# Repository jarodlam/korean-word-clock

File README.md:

# Korean word clock
A wall-mounted clock that reads out the current time in Korean.

## Bill of materials
* Raspberry Pi Pico
    * [Core Electronics](https://core-electronics.com.au/raspberry-pi-pico.html)
* Pimoroni RV3028 Breakout
    * [Core Electronics](https://core-electronics.com.au/pimoroni-rv3028-real-time-clock-rtc-breakout.html)
* Adafruit USB-C Breakout
    * [Core Electronics](https://core-electronics.com.au/adafruit-usb-c-breakout-board-downstream-connection.html)
* 1000 uF electrolytic capacitor
    * [Core Electronics](https://core-electronics.com.au/electrolytic-decoupling-capacitors-1000uf-25v.html)
* 1N4733A 5.1 V Zener diode
    * [Core Electronics](https://core-electronics.com.au/zener-diode-5-1v-1w.html)
    * [Jaycar](https://www.jaycar.com.au/5-1v-1n4733-1-watt-zener-diode/p/ZR1403)
* LED 3-pin JST-SM pigtail connectors
    * [Core Electronics](https://core-electronics.com.au/led-strip-pigtail-connector-3-pin.html)
* 12mm momentary push button
    * [Core Electronics](https://core-electronics.com.au/momentary-push-button-switch-12mm-square.html)
    * [Jaycar](https://www.jaycar.com.au/spst-pcb-mount-tactile-switch-round/p/SP0609)

## Translations
Korean | English
------ | -------
한시 | one o'clock
두시 | two o'clock
세시 | three o'clock
네시 | four o'clock
다섯시 | five o'clock
여섯시 | six o'clock
일곱시 | seven o'clock
여덟시 | eight o'clock
아홉시 | nine o'clock
열시 | ten o'clock
열한시 | eleven o'clock
열두시 | twelve o'clock
자정 | midnight
정오 | noon
오분 | five minutes
십분 | ten minutes
이십분 | twenty minutes
삼십분 | thirty minutes
사십분 | forty minutes
오십분 | fifty minutes

## Acknowledgements
* [HangulClock](https://suapapa.github.io/site-hangulclocks/) by Homin Lee
* [Raspberry Pi Pico EAGLE library](https://github.com/Lobo-T/RPI-Pico-Eagle-lib) by Lobo-T
* [pi_pico_neopixel](https://github.com/blaz-r/pi_pico_neopixel) MicroPython library by Blaž Rolih
* [rv3028-python](https://github.com/pimoroni/rv3028-python) MicroPython library by Pimoroni

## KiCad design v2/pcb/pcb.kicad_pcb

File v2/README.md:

# Korean word clock v2
A wall-mounted clock that reads out the current time in Korean.

Change log from v1:
- Uses an ATmega32U4 microcontroller instead of the RP2040. 
- PCB is drawn in KiCad instead of EAGLE.

## Bill of materials
* SparkFun Qwiic Pro Micro
    * [Core Electronics](https://core-electronics.com.au/sparkfun-qwiic-pro-micro-usb-c-atmega32u4.html)
    * [Mouser](https://au.mouser.com/ProductDetail/SparkFun/DEV-15795?qs=vHuUswq2%252BszUNhUhTg0rsg%3D%3D)
* Pimoroni RV3028 Breakout
    * [Core Electronics](https://core-electronics.com.au/pimoroni-rv3028-real-time-clock-rtc-breakout.html)
    * [Mouser](https://au.mouser.com/ProductDetail/Pimoroni/PIM449?qs=GedFDFLaBXE4W0MVwPUjCA%3D%3D)
* LED 3-pin JST-SM pigtail connector
    * [Core Electronics](https://core-electronics.com.au/led-strip-pigtail-connector-3-pin.html)
    * [Mouser](https://au.mouser.com/ProductDetail/Adafruit/1663?qs=GURawfaeGuBbzkAfeSrhnA%3D%3D)
* 12mm momentary push buttons
    * [Core Electronics](https://core-electronics.com.au/momentary-push-button-switch-12mm-square.html)
    * [Mouser](https://au.mouser.com/ProductDetail/SparkFun/COM-09190?qs=WyAARYrbSnYmfgv9mXV0oQ%3D%3D)
    * [Jaycar](https://www.jaycar.com.au/spst-pcb-mount-tactile-switch-round/p/SP0609)
* 4.7k resistors 1.6x3.6 mm
    * [Mouser](https://au.mouser.com/ProductDetail/YAGEO/MFR25SFTF52-4K7?qs=sGAEpiMZZMtlubZbdhIBIGLlr6zM66%2Fae5%252BGZlJpQLw%3D)

## Software

Requirements:

- [PlatformIO](https://platformio.org/)

Usage (run from `src/` directory with `platformio.ini`:

```sh
# Build
$ pio run

# Upload
$ pio run -t upload

# Generate clangd compile_commands.json for LSP
$ pio run -t compiledb -e sparkfun_promicro16

# Clean build files
$ pio run -t clean

# Run local tests
$ pio test -e native

# View serial monitor
$ pio device monitor
```

## Translations
Korean | English
------ | -------
한시 | one o'clock
두시 | two o'clock
세시 | three o'clock
네시 | four o'clock
다섯시 | five o'clock
여섯시 | six o'clock
일곱시 | seven o'clock
여덟시 | eight o'clock
아홉시 | nine o'clock
열시 | ten o'clock
열한시 | eleven o'clock
열두시 | twelve o'clock
자정 | midnight
정오 | noon
오분 | five minutes
십분 | ten minutes
이십분 | twenty minutes
삼십분 | thirty minutes
사십분 | forty minutes
오십분 | fifty minutes

## Acknowledgements and references
* [HangulClock](https://suapapa.github.io/site-hangulclocks/) by Homin Lee
* [Adafruit NeoPixel library](https://github.com/adafruit/Adafruit_NeoPixel)
* [SparkFun KiCad Libraries](https://github.com/sparkfun/SparkFun-KiCad-Libraries)

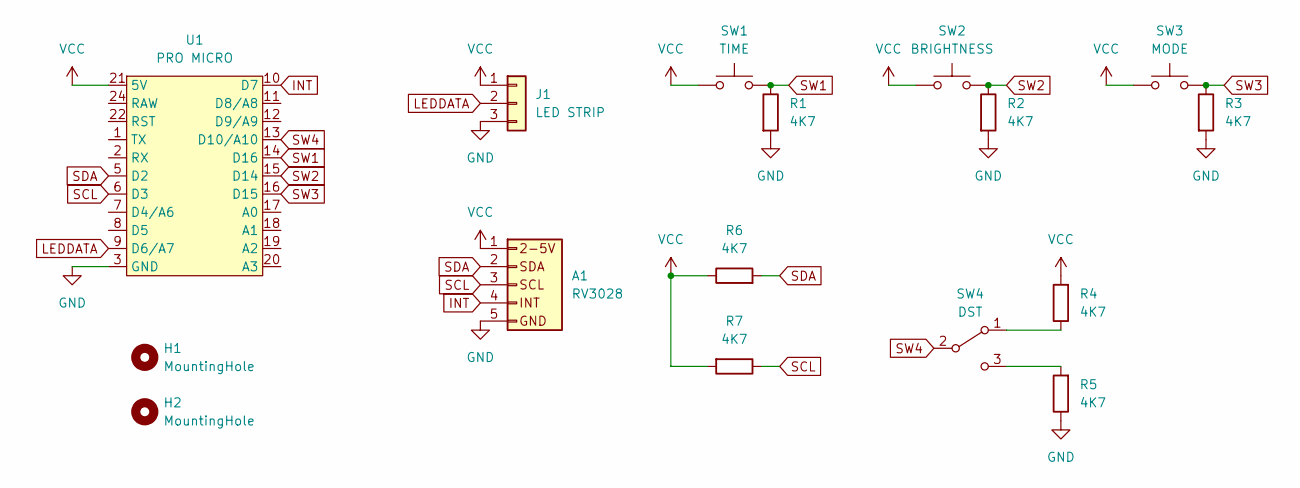
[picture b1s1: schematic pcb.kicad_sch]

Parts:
A1: RV3028; Pimoroni_RV3028_Breakout
H1, H2: MountingHole; MountingHole_3.2mm_M3_Pad
J1: LED STRIP; SolderWire-0.75sqmm_1x03_P4.8mm_D1.25mm_OD2.3mm
R1, R2, R3, R4, R5, R6, R7: 4K7; R_Axial_DIN0204_L3.6mm_D1.6mm_P5.08mm_Horizontal
SW1: TIME; Push_PTH_12x12mm; Mfg Part# EG4904TR-ND
SW2: BRIGHTNESS; Push_PTH_12x12mm; Mfg Part# EG4904TR-ND
SW3: MODE; Push_PTH_12x12mm; Mfg Part# EG4904TR-ND
SW4: DST; Slide_SPDT_PTH_11.6x4.0mm
U1: PRO MICRO; ProMicroC

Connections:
GND: A1.5, J1.3, R1.2, R2.2, R3.2, R5.1, U1.3 (GND), U1.4 (GND), U1.23 (GND)
INT: A1.4, U1.10 (D7)
LEDDATA: J1.2, U1.9 (D6/A7)
unnamed: R4.1, SW4.1 (A)
unnamed: R5.2, SW4.3 (C)
SCL: A1.3, R7.1, U1.6 (D3)
SDA: A1.2, R6.2, U1.5 (D2)
SW1: R1.1, SW1.2, U1.14 (D16)
SW2: R2.1, SW2.2, U1.15 (D14)
SW3: R3.1, SW3.2, U1.16 (D15)
SW4: SW4.2 (B), U1.13 (D10/A10)
VCC: A1.1, J1.1, R4.2, R6.1, R7.2, SW1.1, SW2.1, SW3.1, U1.21 (5V)

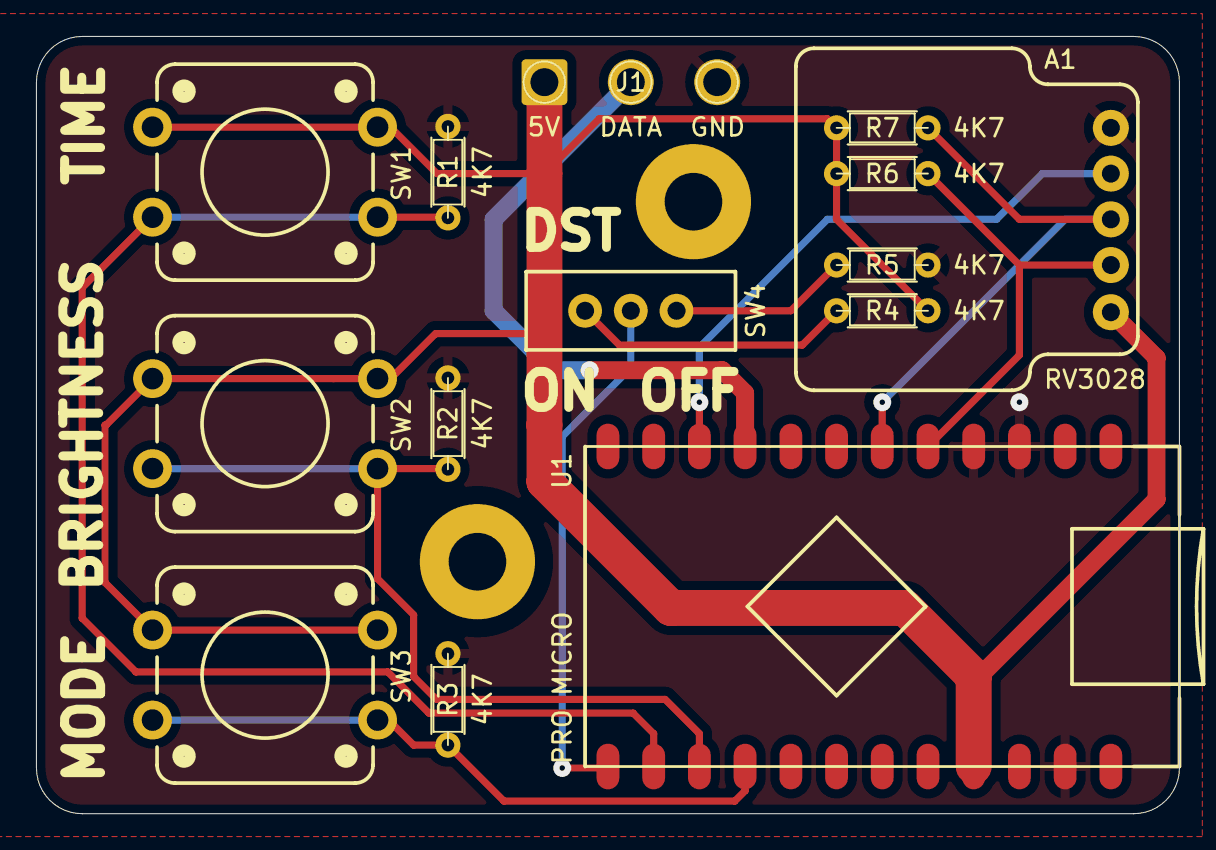
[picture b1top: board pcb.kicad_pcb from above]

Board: 2 copper layers, 63.5 x 43.2 mm, 16 parts (0 on the bottom side), 12 nets.

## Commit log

2022-06-14 [CAD] CAD work in progress
2022-06-14 [CAD] Layer 2 and 3
2022-06-14 [CAD] Most layers done
2022-07-05 [PCB] Initial commit for PCB
2022-08-25 [CAD] Finish 3D design
2022-08-27 [DOC] Updated BOM
2022-08-29 [PCB] Finished design subject to testing
2022-08-29 [DOC] Translations and updated BOM
2022-08-30 [PCB] Sent off for manufacturing
2022-08-30 [CAD] Cutout size for PCB
2022-08-30 [SRC] Start on code
2022-08-30 [DOC] More translations
2022-09-14 [CAD] Mostly final design, need to fix front grid spacing
2022-09-14 [LASER] Start work on laser layout
2022-09-14 [CAD] Fix grid spacing
2022-09-14 [LASER] Final layout
2022-09-24 [SRC] RV2038 interface class
2022-09-24 [SRC] ClockFace class and effects
2022-09-25 [SRC] Button hook up and fast-forwarding
2022-09-25 [SRC] Move ButtonInput to a separate file
2022-09-25 [SRC] Scheduling system
2022-09-25 [SRC] Birthday effect and better rainbow effect
2022-09-30 [SRC] Set time script
2022-09-30 [SRC] Save settings to RTC EEPROM and more effects
2022-10-04 [SRC] Switch daylight savings on/off using switch
2023-06-25 [DOC] Change title
2024-11-22 [CHORE] Add v2
2024-11-22 [PCB] Start v2 PCB
2024-11-22 [DOC] Add additional BOM
2024-11-27 [PCB] New PCB mostly complete
2024-11-29 [DOC] Correct resistor
2024-11-29 [PCB] Final design and gerber
2025-01-11 [SRC] Button implementation
2025-01-12 [SRC] Port RV3028 library
2025-01-12 [SRC] RTC fully working
2025-03-29 [SRC] LED matrix code
2025-09-28 [SRC] Use PlatformIO
2025-09-28 [SRC] Run clang-format
2025-10-01 [SRC] Add Nix
2025-10-04 wip 2
2025-10-04 wip 3
2025-10-04 wip 4 (working)
2025-10-05 uploading!
2025-10-05 it works
2025-10-05 [SRC] KoreanClockFace implementation, refactor, tests
    wip 2
    wip 3
    wip 4 (working)
    uploading!
    it works
2025-10-05 [CHORE] Add Nix
2025-10-26 [SRC] clang-format
2025-10-27 [SRC] buttons wip
2025-10-27 [SRC] make buttons work
2025-12-17 [CAD] v2 mods
2025-12-17 [LASER] exports
2026-01-03 [LASER] layout
